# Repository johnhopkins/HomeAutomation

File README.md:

# HomeAutomation
A home automation project allowing control of lighting, heating and other appliances around the home with various sensors and actuators.

## Temperature Sensor
This code was taken from [bildr.org] (http://bildr.org/2011/07/ds18b20-arduino/) and adapted to suit. It is an arduino sketch that with some very basic wiring and a DS18B20 temperature chip will measure the temperature in that location and feed the data serially via the usb cable to be read by the serial reader.

## TRV
There are several wireless thermostatic radiator valves on the market. Some research is required as to which ones are open or the easiest to hack. Current favourite is the Energeneie range due to the fact they offer raspberry pi connectivity.

## Light Switch

Control for lighting in and around the home with a simple on off protocol, will be added here.

## Socket Switch

Control of sockets with a simple on off protocol, will be added here.

## Other appliances and Sensors

PIR's, proximity and geo location capabilities will go under this heading.

# Gateway

The gateway will act as a server for the web interface, and will drive all the wireless modules so needs to act as both reciever and transmitter. All data recieved will be passed to the server for processing. All commands to controllable sensors and actuators will be sent from the gateway.

## Serial Reader
This is a simple python module which reads the serial data from the usb port (or any port specified). It then parses the serial data and stores the information in the mongo database, for use with the web interface as required.

## Boiler Control
This very simply turns on and off the boiler via RF. The file is an arduino sketch which requires a 433MHz transmitter set up. I aim to add the schematics for this soon. N.B. This sketch works on my home boiler a Worcester Bosch Greenstar 30CDi combi boiler. I sniffed the codes from my thermostat to find the on off codes, and this file has been constructed to suit my boiler. I believe that all the thermostat and boiler pairings have unique codes, so this will probably not work with your boiler. Likewise if your boiler operates on a different radio frequency then adaptations to the code will be required to make it work for you. I will eventually put a write up on here as to how I hacked this to work. Get in touch in the meantime if you would like to know how I did it. I don't see any reason this code cannot be adapted to suit any make of boiler on any frequency as long as you have the hardware to do it.

## Flaskapp
'Mighty oaks from small acorns grow'.
This is the beginnings of the 'front end' of this homeautomation system. So far it displays the temperature from a temperature sensor, and plots a graph of historic temperature data upto the current time. Plenty to do here.

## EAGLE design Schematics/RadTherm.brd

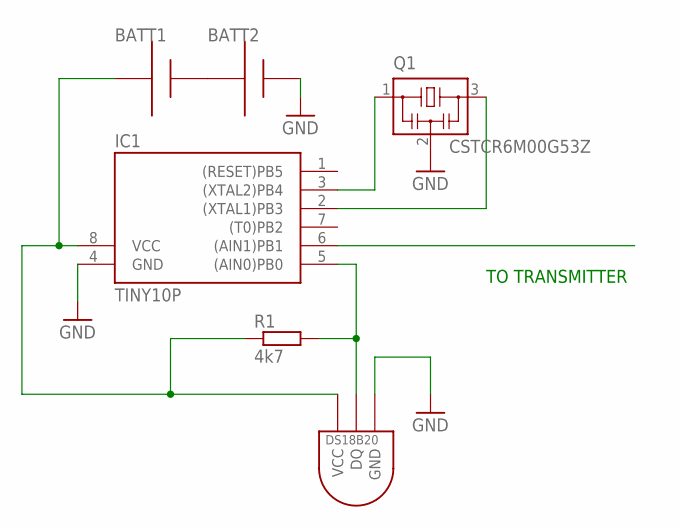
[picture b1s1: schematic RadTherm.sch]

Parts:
BATT1, BATT2: AAA; 12BH412
IC1: TINY10P; DIL08
Q1: CSTCR6M00G53Z; CSTCR6M
R1: 4k7; 0204/7
U$1: DS1820TO92; DS1820

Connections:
GND: BATT2.+, IC1.4 (GND), Q1.2, U$1.GND
unnamed: BATT1.+, BATT2.-
unnamed: IC1.3 ((XTAL2)PB4), Q1.1
unnamed: IC1.2 ((XTAL1)PB3), Q1.3
unnamed: IC1.5 ((AIN0)PB0), R1.2, U$1.DQ
unnamed: BATT1.-, IC1.8 (VCC), R1.1, U$1.VDD (VCC)

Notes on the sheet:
TO TRANSMITTER

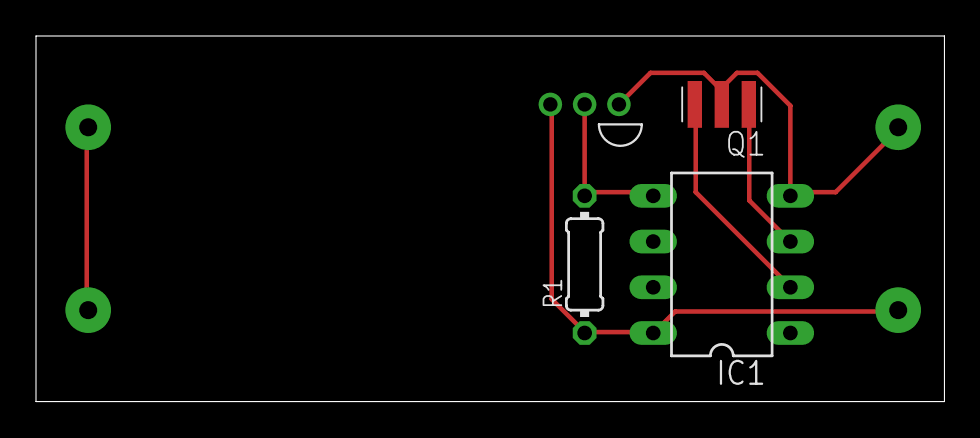
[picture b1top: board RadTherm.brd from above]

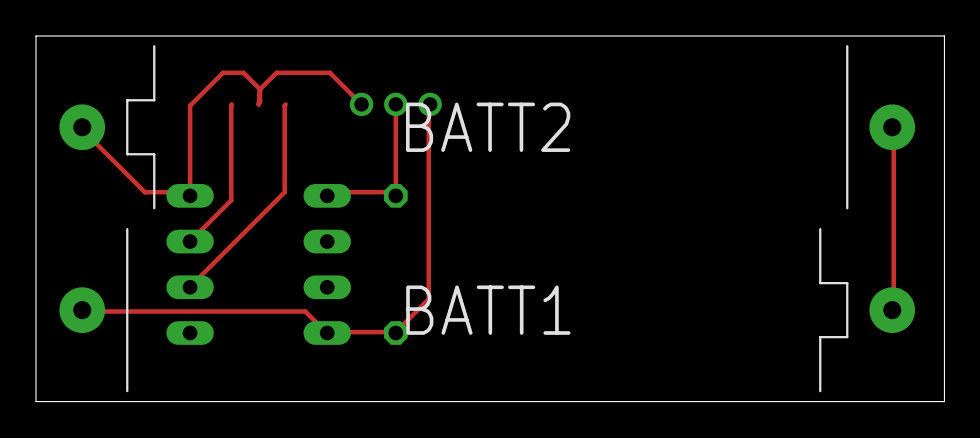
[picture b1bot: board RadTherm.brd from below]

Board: 2 copper layers, 50.5 x 20.3 mm, 6 parts (2 on the bottom side), 6 nets.

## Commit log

2016-01-19 Added boiler, serial read and tempsensor basics
2016-01-19 Include .gitignore
2016-01-19 Added Flask webapp to display recorded temps
2016-01-19 Changed .gitignore
2016-01-19 clean up
2016-01-19 changed info in serialRead
2016-01-19 Added schematic of Radio Thermometer
2016-01-19 Added eagle board file
2016-01-19 Created todo file
2016-01-19 renamed files and folder
2016-01-26 Exlude virtualenv's
2016-01-31 removed test.txt
2016-06-18 minor additions
